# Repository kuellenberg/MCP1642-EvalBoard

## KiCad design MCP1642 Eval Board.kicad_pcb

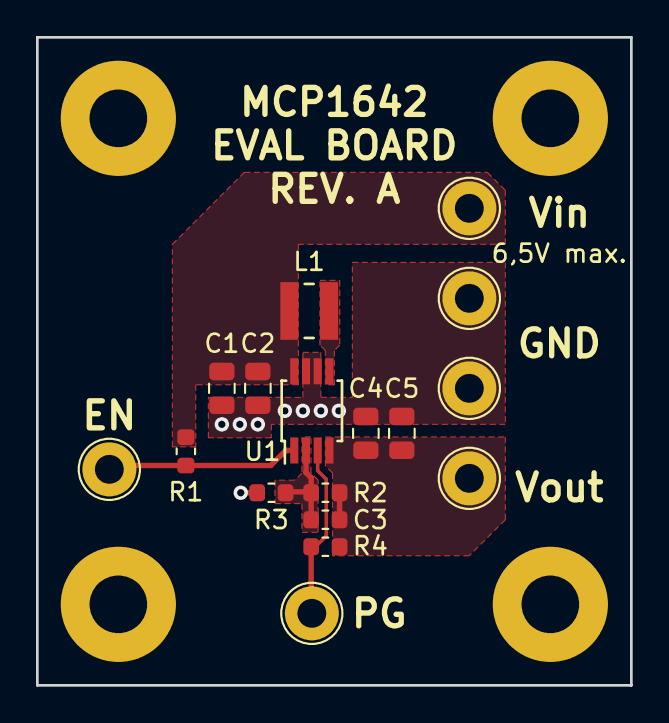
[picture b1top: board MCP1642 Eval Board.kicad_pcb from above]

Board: 2 copper layers, 33.0 x 36.0 mm, 22 parts (1 on the bottom side), 7 nets.

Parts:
C1, C2, C4, C5: 4.7uF; C_0805_2012Metric
C3: 27pF; C_0603_1608Metric
G1: Lemonhead; lemonhead
H1, H2, H3, H4: MountingHole_Pad; MountingHole_3.2mm_M3_Pad
J1: VIN; TestPoint_Loop_D2.60mm_Drill1.6mm_Beaded
J2, J5: GND; TestPoint_Loop_D2.60mm_Drill1.6mm_Beaded
J3: EN; TestPoint_Loop_D2.60mm_Drill1.6mm_Beaded
J4: VOUT; TestPoint_Loop_D2.60mm_Drill1.6mm_Beaded
J6: PG; TestPoint_Loop_D2.60mm_Drill1.6mm_Beaded
L1: 4.7uH; WE-TPC-2828
R1, R4: 1M; R_0603_1608Metric
R2, R3: R; R_0603_1608Metric
U1: MCP1642BD-ADJ; MSOP-8_3x3mm_P0.65mm

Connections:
/EN: J3.1, R1.2, U1.1
/PG: J6.1, R4.2, U1.3
/VIN: C1.1, C2.1, J1.1, L1.1, R1.1, U1.8
/VOUT: C3.1, C4.1, C5.1, J4.1, R2.1, R4.1, U1.4
GND: C1.2, C2.2, C4.2, C5.2, H1.1, H2.1, H3.1, H4.1, J2.1, J5.1, R3.2, U1.6, U1.7
unnamed: C3.2, R2.2, R3.1, U1.2
unnamed: L1.2, U1.5
